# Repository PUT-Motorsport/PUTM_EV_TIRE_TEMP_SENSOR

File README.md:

# Tire Temperature Sensor v3.0

**TTS** (Tire Temperature Sensor) is a PCB designed to measure the temperature quickly, at a distance, and without the need to touch the wheels. The 4x16 pixel IR camera is used to obtain the data. It communicates with the STM microprocessor via the I2C protocol. Data is then averaged out to a 1x8 array of unsigned ints and sent with the CAN Transceiver to the car’s CAN network. This array can be then read off of the telemetry system implemented in the PM-08 racing car.

## Applications

While driving, a tire heats up. Heat dissipates differently across its surface and its rate changes depending on many factors (E.g. weather conditions or reoccurring acceleration). As a tire has its maximal temperature, exceeding this value may weaken its structural strength and cause its destruction in the worst-case scenario. This IR Camera PCB makes it possible to monitor a tire across its whole surface and prevent any damage associated with the temperature. As TTS monitors every wheel out of 4, our crew can easily detect if tires wear unevenly or excessively. Tire temperature patterns inform whether the car is properly calibrated, as the out-of-tune suspension causes tires to heat up significantly faster. This may result in grip loss in these areas.

## Core features

* 4x16 pixel MLX90621 thermal camera
* STM32G0C1KCT
* 24V to 3.3V buck converter
* 3.3V to 2.6V LDO
* 3.3V Isolated CAN transceiver
* Overcurrent and reverse polarity protection
* Status LEDs

## PCB

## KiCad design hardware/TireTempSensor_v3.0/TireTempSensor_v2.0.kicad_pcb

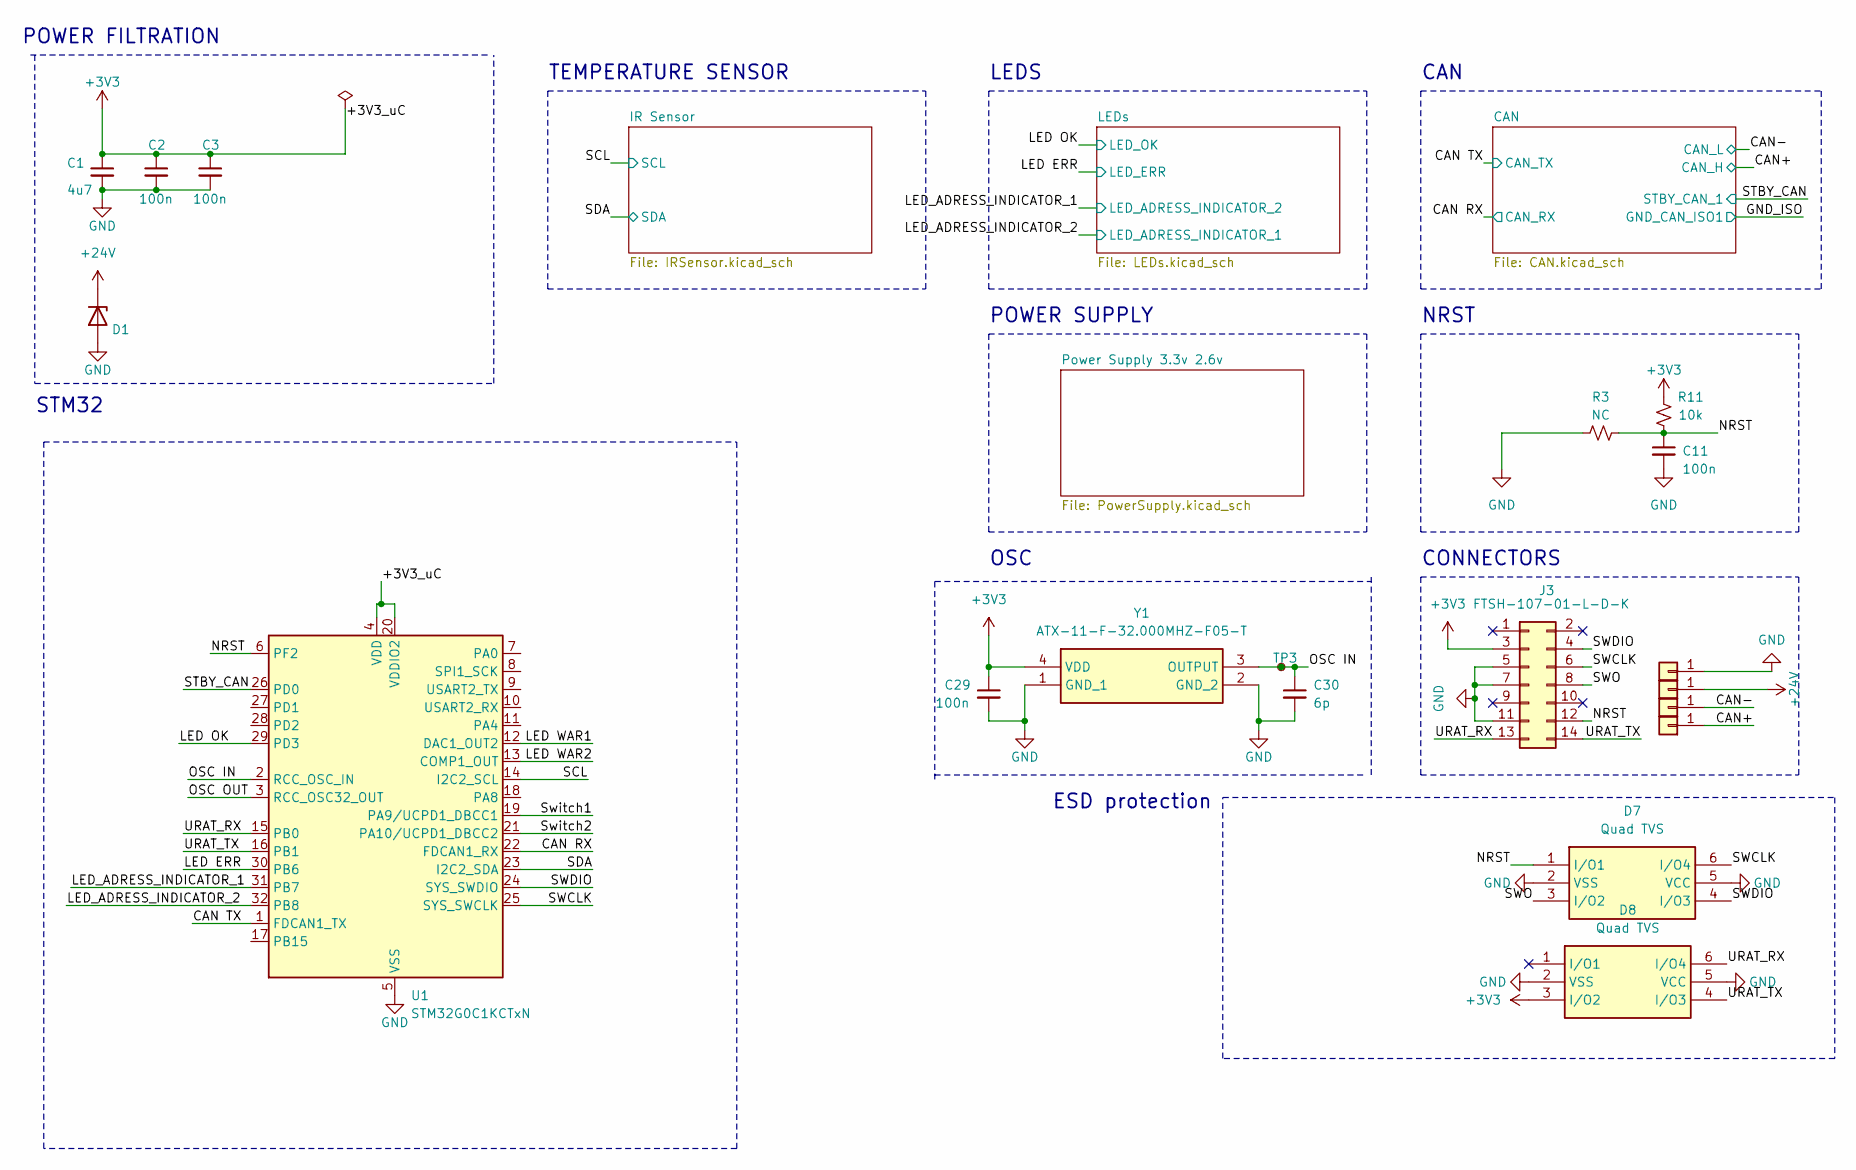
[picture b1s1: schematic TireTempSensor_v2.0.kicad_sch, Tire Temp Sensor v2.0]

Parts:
C1: 4u7; C_0603_1608Metric_Pad1.08x0.95mm_HandSolder; Mouser Part Number 81-ZRB18AR6YA475KE5L
C2, C3, C11, C29: 100n; C_0603_1608Metric_Pad1.08x0.95mm_HandSolder; Mouser Part Number 81-GCJ188R71H104MA2D
C30: 6p; C_0603_1608Metric_Pad1.08x0.95mm_HandSolder
D1: 30V; D_SOD-123
D7, D8: Quad TVS; SOT95P285X140-6N; Mouser Part Number 621-D5V0P4UR6SO-7
J1, J2, J4, J5: Conn_01x01; SolderWire-0.1sqmm_1x01_D0.4mm_OD1mm_Relief
J3: FTSH-107-01-L-D-K; FTSH-107-XX-YYY-DV-K; Mouser Part Number 200-FTSH10701LDK
R3: NC; R_0402_1005Metric
R11: 10k; R_0603_1608Metric
TP3: TestPoint_Small; TestPoint_Pad_D1.0mm
U1: STM32G0C1KCTxN; LQFP-32_7x7mm_P0.8mm
Y1: ATX-11-F-32.000MHZ-F05-T; ATX11F32000MHZF05T; Mouser Part Number 815-ATX11F32000MF05T

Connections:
+3V3: C1.1, C2.1, C3.1, C29.1, D8.3 (I/O2), J3.3, R11.2, U1.4 (VDD), U1.20 (VDDIO2), Y1.4 (VDD); also elsewhere on the board
+24V: D1.1 (K), J2.1; also elsewhere on the board
/CAN RX: U1.22 (FDCAN1_RX); also elsewhere on the board
/CAN TX: U1.1 (FDCAN1_TX); also elsewhere on the board
/CAN+: J5.1; also elsewhere on the board
/CAN-: J4.1; also elsewhere on the board
/LED ERR: U1.30 (PB6); also elsewhere on the board
/LED OK: U1.29 (PD3); also elsewhere on the board
/LED WAR1: U1.12 (DAC1_OUT2)
/LED WAR2: U1.13 (COMP1_OUT)
/LED_ADRESS_INDICATOR_1: U1.31 (PB7); also elsewhere on the board
/LED_ADRESS_INDICATOR_2: U1.32 (PB8); also elsewhere on the board
/NRST: C11.1, D7.1 (I/O1), J3.12, R3.2, R11.1, U1.6 (PF2)
/OSC IN: C30.1, TP3.1, U1.2 (RCC_OSC_IN), Y1.3 (OUTPUT)
/OSC OUT: U1.3 (RCC_OSC32_OUT)
/SCL: U1.14 (I2C2_SCL); also elsewhere on the board
/SDA: U1.23 (I2C2_SDA); also elsewhere on the board
/STBY_CAN: U1.26 (PD0); also elsewhere on the board
/SWCLK: D7.6 (I/O4), J3.6, U1.25 (SYS_SWCLK)
/SWDIO: D7.4 (I/O3), J3.4, U1.24 (SYS_SWDIO)
/SWO: D7.3 (I/O2), J3.8
/Switch1: U1.19 (PA9/UCPD1_DBCC1)
/Switch2: U1.21 (PA10/UCPD1_DBCC2)
/URAT_RX: D8.6 (I/O4), J3.13, U1.15 (PB0)
/URAT_TX: D8.4 (I/O3), J3.14, U1.16 (PB1)
GND: C1.2, C2.2, C3.2, C11.2, C29.2, C30.2, D1.2 (A), D7.2 (VSS), D7.5 (VCC), D8.2 (VSS), D8.5 (VCC), J1.1, J3.5, J3.7, J3.11, R3.1, U1.5 (VSS), Y1.1 (GND_1), Y1.2 (GND_2); also elsewhere on the board

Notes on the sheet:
NRST
POWER SUPPLY
ESD protection
OSC
STM32
CAN
POWER FILTRATION
LEDS
CONNECTORS
TEMPERATURE SENSOR

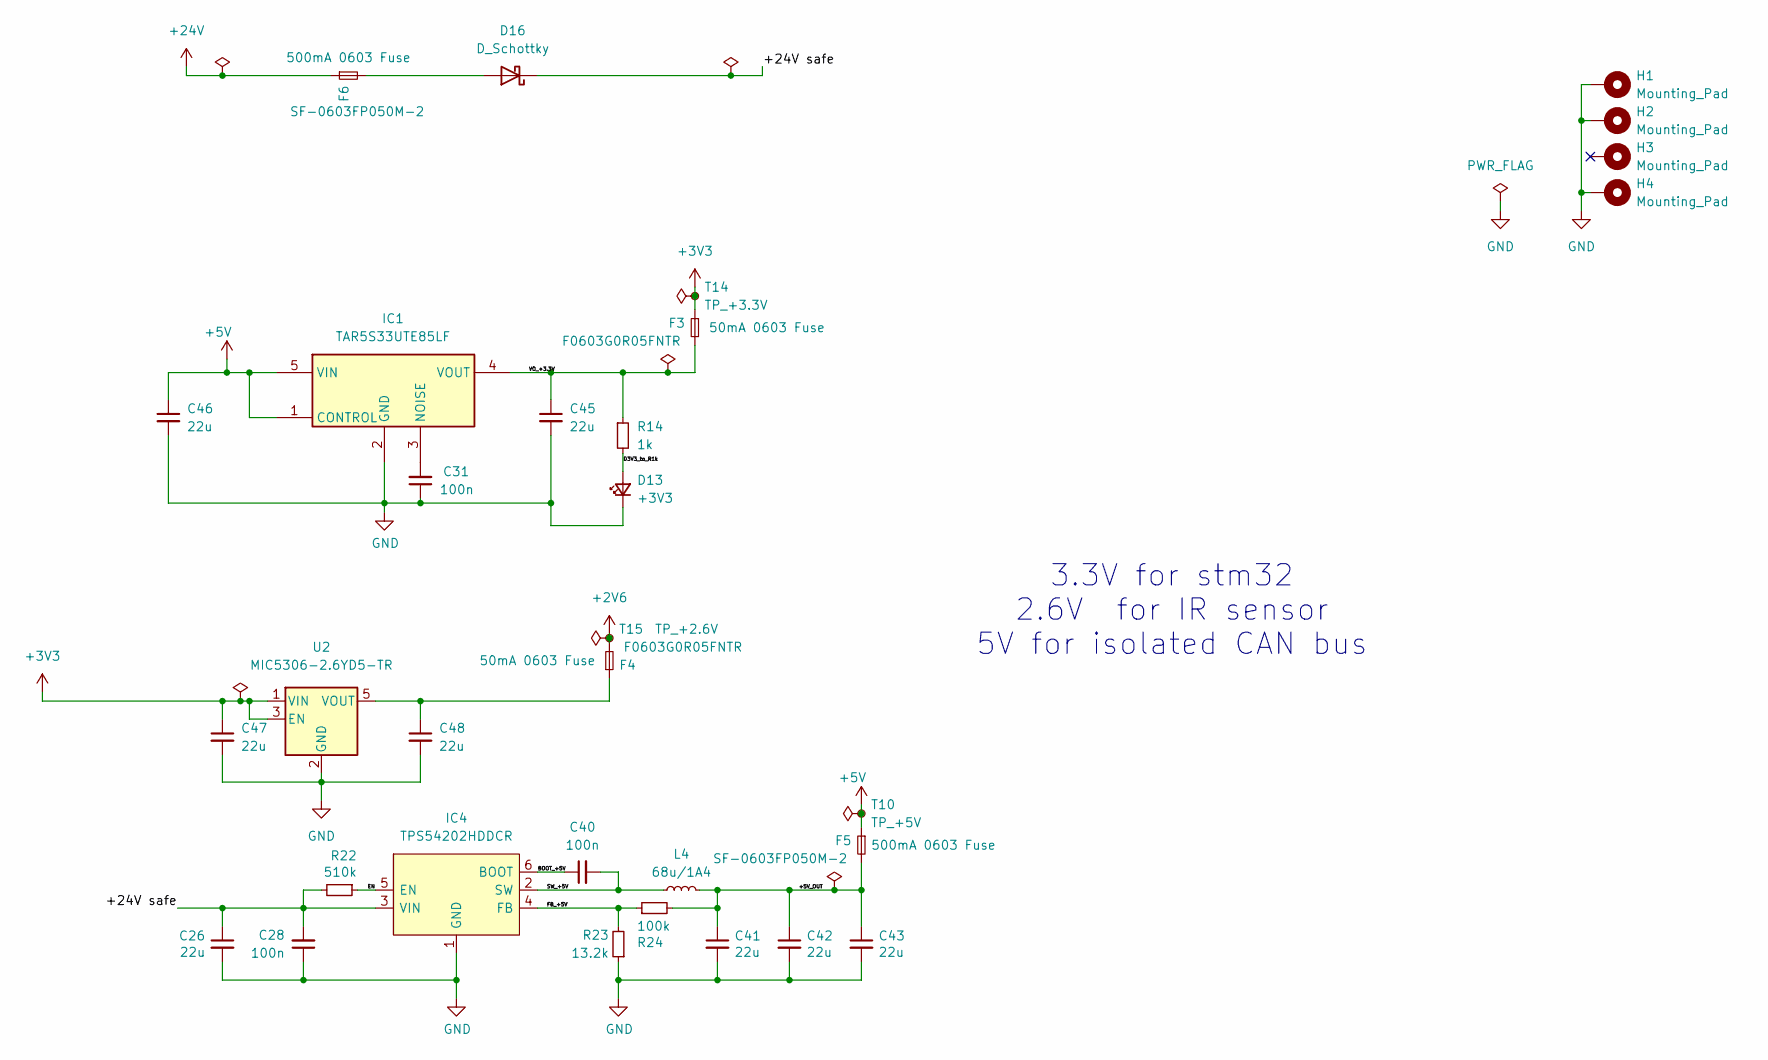
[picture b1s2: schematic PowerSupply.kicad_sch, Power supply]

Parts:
C26, C41, C42, C43: 22u; C_0805_2012Metric_Pad1.18x1.45mm_HandSolder; Manufacturer_Part_Number CL21A107MQYNNWE; Mouser Part Number 81-ZRA21CR61E226ME1L
C28, C31: 100n; C_0603_1608Metric_Pad1.08x0.95mm_HandSolder; Manufacturer_Part_Number C0603C104J3RACTU; Mouser Part Number 81-GCJ188R71H104MA2D
C40: 100n; C_0603_1608Metric_Pad1.08x0.95mm_HandSolder; Mouser Part Number 81-GCJ188R71H104MA2D
C45, C46, C47, C48: 22u; C_0805_2012Metric_Pad1.18x1.45mm_HandSolder; Mouser Part Number 81-ZRA21CR61E226ME1L
D13: +3V3; LED_0603_1608Metric_Pad1.05x0.95mm_HandSolder
D16: D_Schottky; D_0603_1608Metric_Pad1.05x0.95mm_HandSolder
F3, F4: F0603G0R05FNTR; Fuse_0603_1608Metric_Pad1.05x0.95mm_HandSolder
F5, F6: SF-0603FP050M-2; Fuse_0603_1608Metric_Pad1.05x0.95mm_HandSolder
H1, H2, H3, H4: Mounting_Pad; MountingHole_2.7mm_M2.5_ISO14580_Pad
IC1: TAR5S33UTE85LF; SOTFL65P210X75-5N; Mouser Part Number 757-TAR5S33UTE85LF
IC4: TPS54202HDDCR; SOT-23-6_Handsoldering; Mouser Part Number 595-TPS54202HDDCR
L4: 68u/1A4; L_Vishay_IFSC-1515AH_4x4x1.8mm; Mouser Part Number 810-VLS6045EX-680M
R14: 1k; R_0603_1608Metric_Pad0.98x0.95mm_HandSolder
R22: 510k; R_0603_1608Metric_Pad0.98x0.95mm_HandSolder; Manufacturer_Part_Number RT0603DRD07510KL; Mouser Part Number 603-RT0603DRD07510KL
R23: 13.2k; R_0603_1608Metric_Pad0.98x0.95mm_HandSolder; Manufacturer_Part_Number RT0603DRE0713K3L; Mouser Part Number 603-RT0603DRE0713K3L
R24: 100k; R_0603_1608Metric_Pad0.98x0.95mm_HandSolder; Manufacturer_Part_Number RT0603DRE07100KL; Mouser Part Number 603-RT0603DRE07100KL
T10: TP_+5V; TestPoint_Pad_1.0x1.0mm
T14: TP_+3.3V; TestPoint_Pad_1.0x1.0mm
T15: TP_+2.6V; TestPoint_Pad_1.0x1.0mm
U2: MIC5306-2.6YD5-TR; SOT-23-5

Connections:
+2V6: F4.2, T15.1; also elsewhere on the board
+3V3: C47.1, F3.1, T14.1, U2.1 (VIN), U2.3 (EN); also elsewhere on the board
+5V: C46.1, F5.1, IC1.1 (CONTROL), IC1.5 (VIN), T10.1; also elsewhere on the board
+24V: F6.1; also elsewhere on the board
/Power Supply 3.3v 2.6v/+5V_OUT: C41.1, C42.1, C43.1, F5.2, L4.2, R24.2
/Power Supply 3.3v 2.6v/+24V safe: C26.1, C28.2, D16.1 (K), IC4.3 (VIN), R22.2
/Power Supply 3.3v 2.6v/BOOT_+5V: C40.1, IC4.6 (BOOT)
/Power Supply 3.3v 2.6v/D3V3_to_R1k: D13.2 (A), R14.2
/Power Supply 3.3v 2.6v/EN: IC4.5 (EN), R22.1
/Power Supply 3.3v 2.6v/FB_+5V: IC4.4 (FB), R23.2, R24.1
/Power Supply 3.3v 2.6v/SW_+5V: C40.2, IC4.2 (SW), L4.1
/Power Supply 3.3v 2.6v/VO_+3.3V: C45.1, F3.2, IC1.4 (VOUT), R14.1
GND: C26.2, C28.1, C31.1, C41.2, C42.2, C43.2, C45.2, C46.2, C47.2, C48.2, D13.1 (K), H1.1, H2.1, H4.1, IC1.2 (GND), IC4.1 (GND), R23.1, U2.2 (GND); also elsewhere on the board
unnamed: D16.2 (A), F6.2
unnamed: C31.2, IC1.3 (NOISE)
unnamed: C48.1, F4.1, U2.5 (VOUT)

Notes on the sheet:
3.3V for stm32 2.6V for IR sensor 5V for isolated CAN bus

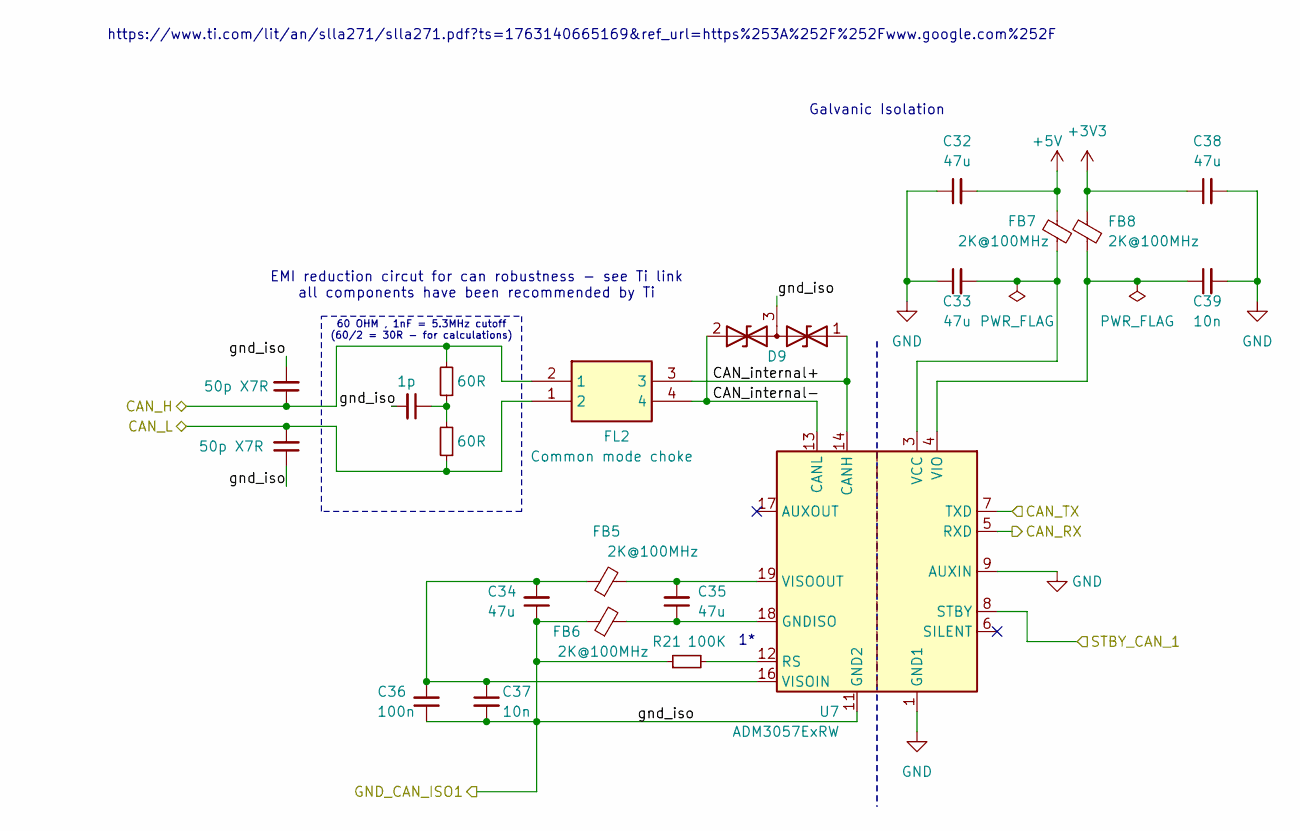
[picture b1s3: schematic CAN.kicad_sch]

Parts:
C32, C33, C34, C35, C38: 47u; C_0805_2012Metric_Pad1.18x1.45mm_HandSolder
C36: 100n; C_0603_1608Metric_Pad1.08x0.95mm_HandSolder; Mouser Part Number 81-GCJ188R71H104MA2D
C37, C39: 10n; C_0603_1608Metric_Pad1.08x0.95mm_HandSolder
C44: 1p; C_0805_2012Metric_Pad1.18x1.45mm_HandSolder
C50, C51: 50p X7R; C_0805_2012Metric_Pad1.18x1.45mm_HandSolder
D9: D_TVS_Dual_AAC; SOT-23_Handsoldering
FB5, FB6, FB7, FB8: 2K@100MHz; L_0805_2012Metric_Pad1.05x1.20mm_HandSolder
FL2: Common mode choke; DR331513BE; Mouser Part Number 652-DR331-513AE
R21: 100K; R_0603_1608Metric_Pad0.98x0.95mm_HandSolder
R25, R26: 60R; R_0603_1608Metric_Pad0.98x0.95mm_HandSolder
U7: ADM3057ExRW; SOIC-20W_7.5x12.8mm_P1.27mm

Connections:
+3V3: C38.1, FB8.2; also elsewhere on the board
+5V: C32.2, FB7.2; also elsewhere on the board
/CAN RX: U7.5 (RXD); also elsewhere on the board
/CAN TX: U7.7 (TXD); also elsewhere on the board
/CAN+: C51.1, FL2.2 (1), R25.2; also elsewhere on the board
/CAN-: C50.2, FL2.1 (2), R26.1; also elsewhere on the board
/CAN/CAN_internal+: D9.1 (A1), FL2.3, U7.14 (CANH)
/CAN/CAN_internal-: D9.2 (A2), FL2.4, U7.13 (CANL)
/GND_ISO: C34.1, C36.1, C37.2, C44.2, C50.1, C51.2, D9.3 (common), FB6.1, R21.1, U7.11 (GND2), U7.15 (GND2)
/STBY_CAN: U7.8 (STBY); also elsewhere on the board
GND: C32.1, C33.1, C38.2, C39.2, U7.1 (GND1), U7.2 (GND1), U7.9 (AUXIN), U7.10 (GND1); also elsewhere on the board
unnamed: C35.1, FB6.2, U7.18 (GNDISO), U7.20 (GNDISO)
unnamed: C44.1, R25.1, R26.2
unnamed: R21.2, U7.12 (RS)
unnamed: C33.2, FB7.1, U7.3 (VCC)
unnamed: C39.1, FB8.1, U7.4 (VIO)
unnamed: C34.2, C36.2, C37.1, FB5.1, U7.16 (VISOIN)
unnamed: C35.2, FB5.2, U7.19 (VISOOUT)

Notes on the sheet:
EMI reduction circut for can robustness - see Ti link all components have been recommended by Ti
https://www.ti.com/lit/an/slla271/slla271.pdf?ts=1763140665169&ref_url=https%253A%252F%252Fwww.google.com%252F
Galvanic Isolation
60 OHM , 1nF = 5.3MHz cutoff (60/2 = 30R - for calculations)

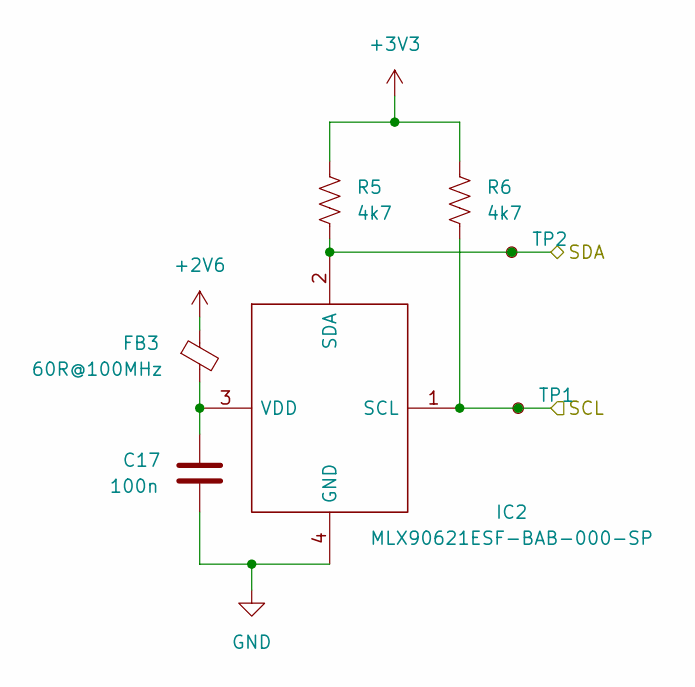
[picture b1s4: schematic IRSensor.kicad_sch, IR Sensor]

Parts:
C17: 100n; C_0603_1608Metric_Pad1.08x0.95mm_HandSolder; Mouser Part Number 81-GCJ188R71H104MA2D
FB3: 60R@100MHz; L_0603_1608Metric
IC2: MLX90621ESF-BAB-000-SP; MLX90621ESFBAB000SP; Manufacturer_Part_Number MLX90621ESF-BAB-000-SP; Mouser Part Number 482-90621ESFBAB000SP
R5, R6: 4k7; R_0603_1608Metric
TP1, TP2: TestPoint_Small; TestPoint_Pad_D1.0mm

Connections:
+2V6: FB3.1; also elsewhere on the board
+3V3: R5.1, R6.1; also elsewhere on the board
/SCL: IC2.1 (SCL), R6.2, TP1.1; also elsewhere on the board
/SDA: IC2.2 (SDA), R5.2, TP2.1; also elsewhere on the board
GND: C17.2, IC2.4 (GND); also elsewhere on the board
unnamed: C17.1, FB3.2, IC2.3 (VDD)

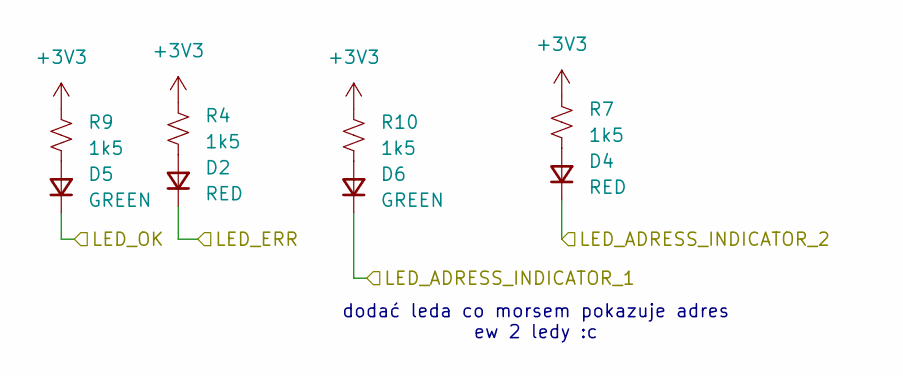
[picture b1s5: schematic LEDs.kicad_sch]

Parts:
D2, D4: RED; D_0603_1608Metric
D5, D6: GREEN; D_0603_1608Metric
R4, R7, R9, R10: 1k5; R_0603_1608Metric

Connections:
+3V3: R4.1, R7.1, R9.1, R10.1; also elsewhere on the board
/LED ERR: D2.1 (K); also elsewhere on the board
/LED OK: D5.1 (K); also elsewhere on the board
/LED_ADRESS_INDICATOR_1: D4.1 (K); also elsewhere on the board
/LED_ADRESS_INDICATOR_2: D6.1 (K); also elsewhere on the board
unnamed: D2.2 (A), R4.2
unnamed: D4.2 (A), R7.2
unnamed: D5.2 (A), R9.2
unnamed: D6.2 (A), R10.2

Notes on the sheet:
dodać leda co morsem pokazuje adres ew 2 ledy :c

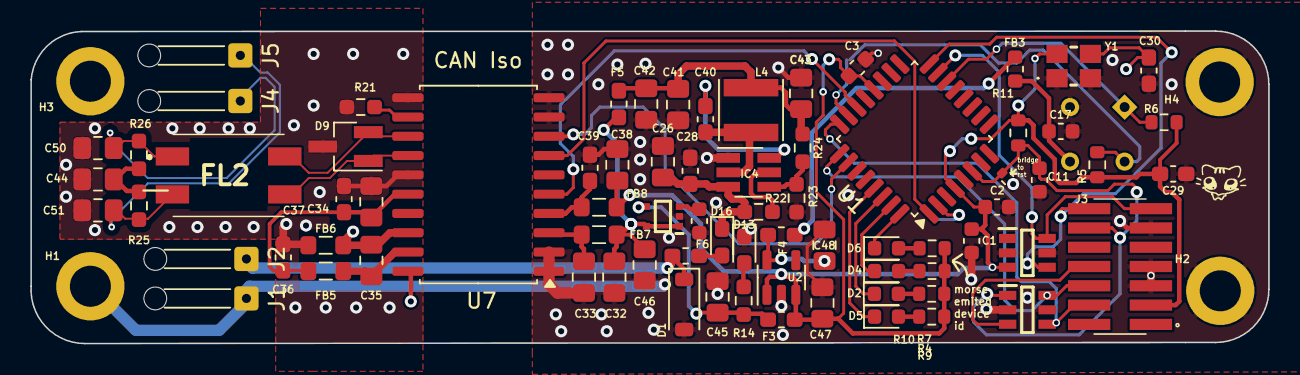
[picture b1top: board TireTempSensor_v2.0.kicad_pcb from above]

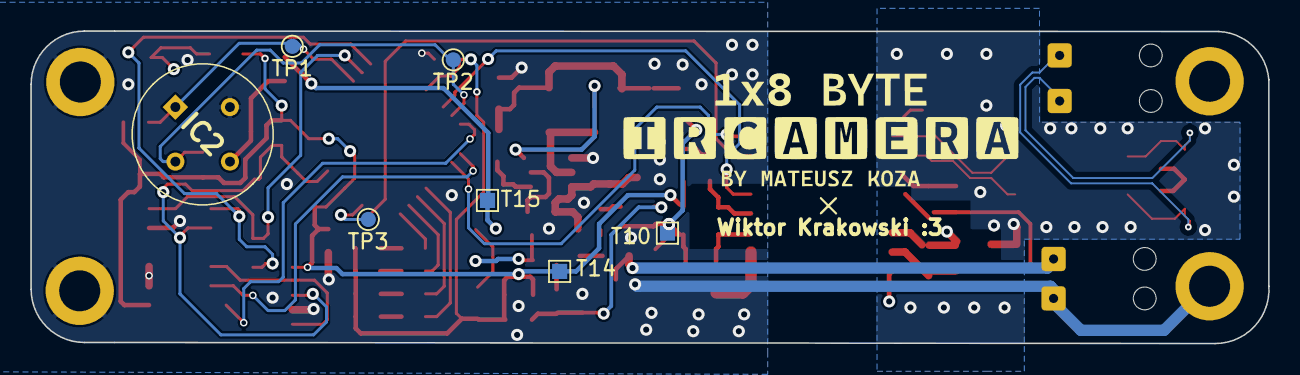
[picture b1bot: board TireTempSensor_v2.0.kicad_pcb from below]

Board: 4 copper layers, 81.5 x 20.6 mm, 87 parts (7 on the bottom side), 49 nets.

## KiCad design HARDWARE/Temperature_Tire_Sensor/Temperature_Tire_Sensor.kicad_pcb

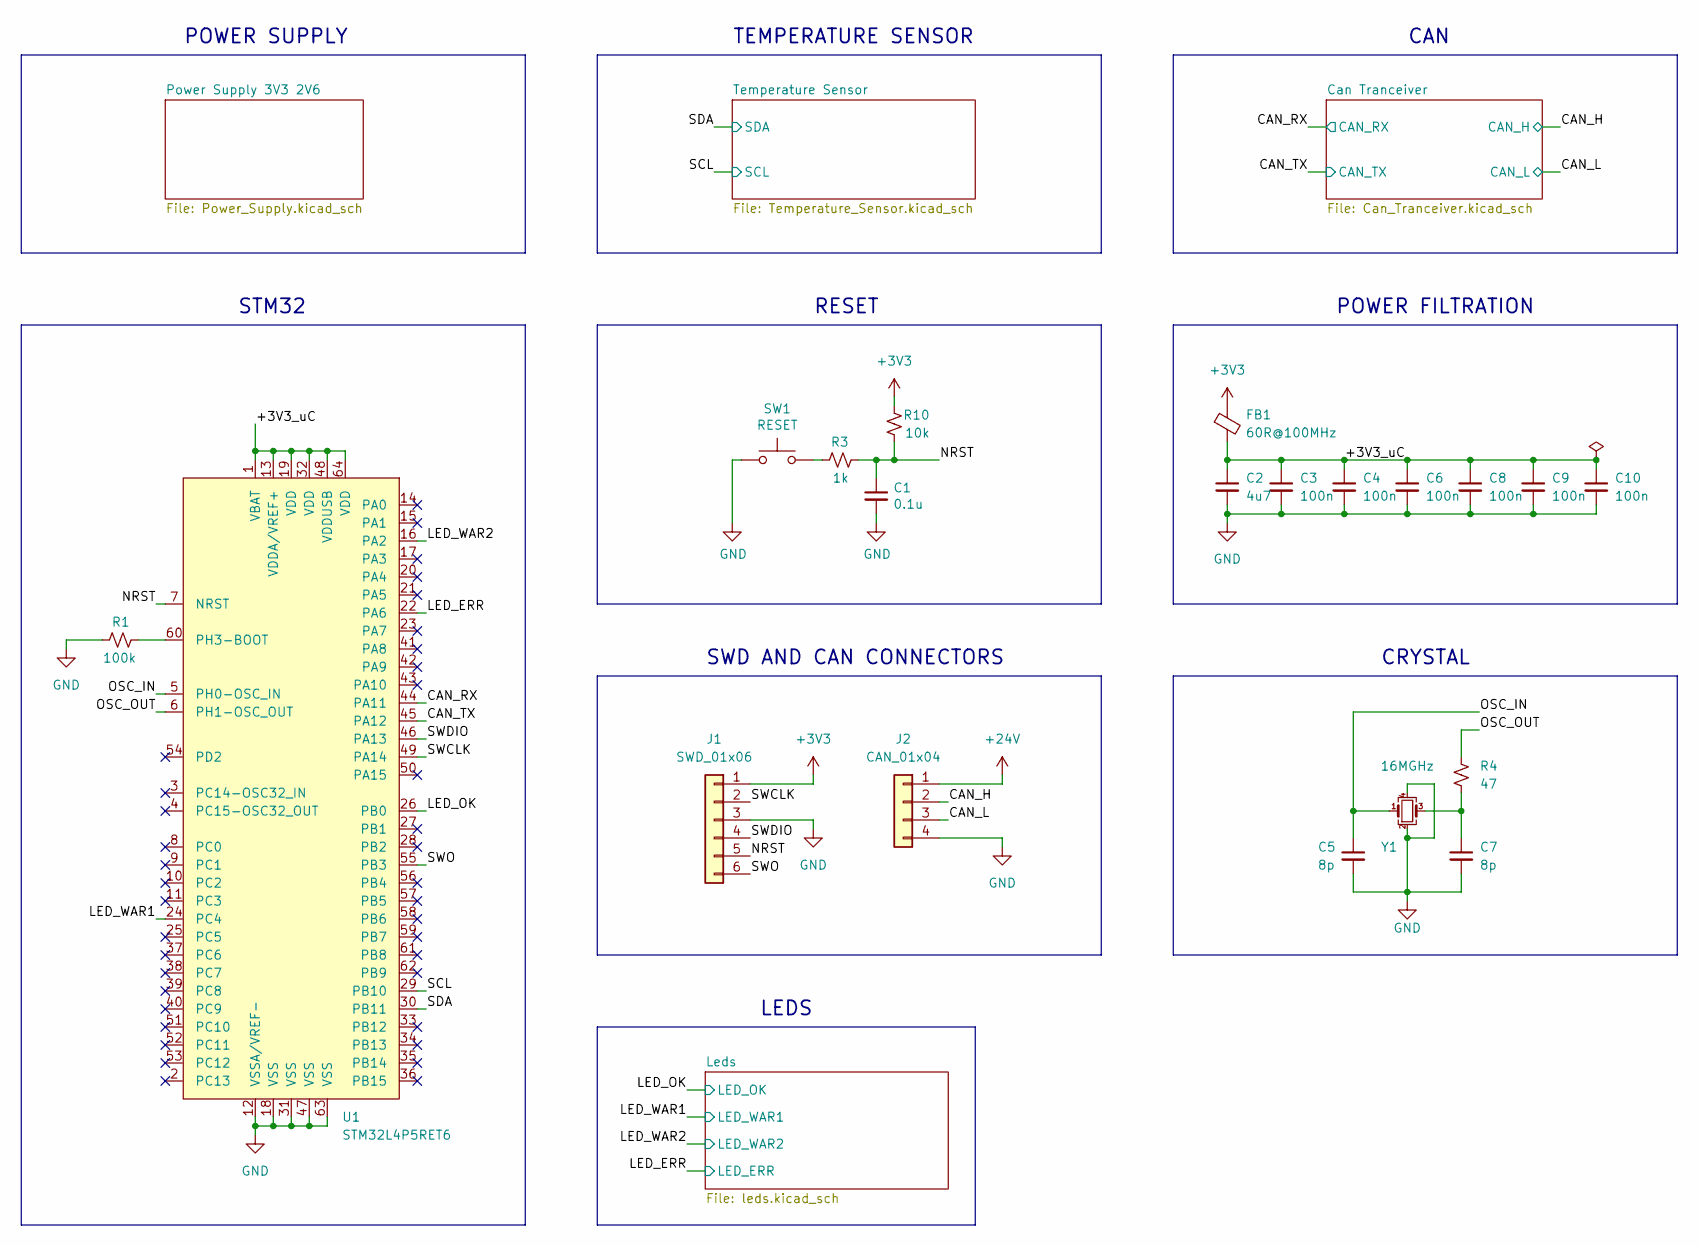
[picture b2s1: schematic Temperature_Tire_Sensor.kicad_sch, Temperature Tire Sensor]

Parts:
C1: 0.1u; C_0603_1608Metric
C2: 4u7; C_0603_1608Metric
C3, C4, C6, C8, C9, C10: 100n; C_0603_1608Metric
C5, C7: 8p; C_0603_1608Metric
FB1: 60R@100MHz; L_0603_1608Metric
J1: SWD_01x06; PinHeader_1x06_P2.54mm_Vertical
J2: CAN_01x04; SolderWirePad_1x04_SMD_1x2mm
R1: 100k; R_0603_1608Metric
R3: 1k; R_0603_1608Metric
R4: 47; R_0603_1608Metric
R10: 10k; R_0603_1608Metric
SW1: RESET; 434781025816
U1: STM32L4P5RET6; LQFP-64_10x10mm_P0.5mm
Y1: 16MGHz; Crystal_SMD_SeikoEpson_TSX3225-4Pin_3.2x2.5mm

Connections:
+3V3: FB1.1, J1.1, R10.2; also elsewhere on the board
+24V: J2.1; also elsewhere on the board
/+3V3_uC: C2.1, C3.1, C4.1, C6.1, C8.1, C9.1, C10.1, FB1.2, U1.1 (VBAT), U1.13 (VDDA/VREF+), U1.19 (VDD), U1.32 (VDD), U1.48 (VDDUSB), U1.64 (VDD)
/CAN_H: J2.2; also elsewhere on the board
/CAN_L: J2.3; also elsewhere on the board
/CAN_RX: U1.44 (PA11); also elsewhere on the board
/CAN_TX: U1.45 (PA12); also elsewhere on the board
/LED_ERR: U1.22 (PA6); also elsewhere on the board
/LED_OK: U1.26 (PB0); also elsewhere on the board
/LED_WAR1: U1.24 (PC4); also elsewhere on the board
/LED_WAR2: U1.16 (PA2); also elsewhere on the board
/NRST: C1.1, J1.5, R3.2, R10.1, U1.7 (NRST)
/OSC_IN: C5.1, U1.5 (PH0-OSC_IN), Y1.1
/OSC_OUT: R4.1, U1.6 (PH1-OSC_OUT)
/SCL: U1.29 (PB10); also elsewhere on the board
/SDA: U1.30 (PB11); also elsewhere on the board
/SWCLK: J1.2, U1.49 (PA14)
/SWDIO: J1.4, U1.46 (PA13)
/SWO: J1.6, U1.55 (PB3)
GND: C1.2, C2.2, C3.2, C4.2, C5.2, C6.2, C7.2, C8.2, C9.2, C10.2, J1.3, J2.4, R1.2, SW1.1, U1.12 (VSSA/VREF-), U1.18 (VSS), U1.31 (VSS), U1.47 (VSS), U1.63 (VSS), Y1.2, Y1.4; also elsewhere on the board
unnamed: C7.1, R4.2, Y1.3
unnamed: R1.1, U1.60 (PH3-BOOT)
unnamed: R3.1, SW1.2

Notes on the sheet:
CAN
CRYSTAL
SWD AND CAN CONNECTORS
TEMPERATURE SENSOR
LEDS
RESET
STM32
POWER FILTRATION
POWER SUPPLY

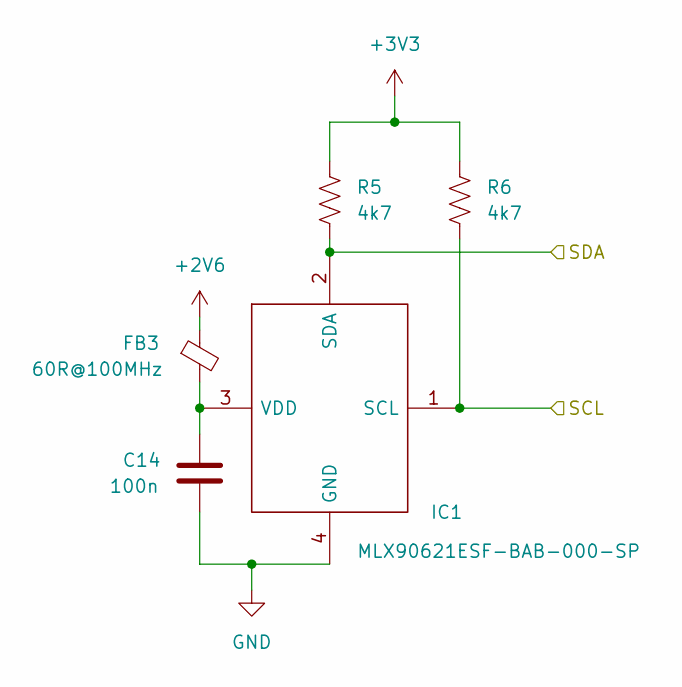
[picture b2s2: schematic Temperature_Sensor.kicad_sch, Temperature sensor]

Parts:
C14: 100n; C_0603_1608Metric
FB3: 60R@100MHz; L_0603_1608Metric
IC1: MLX90621ESF-BAB-000-SP; MLX90621ESFBAB000SP; Manufacturer_Part_Number MLX90621ESF-BAB-000-SP; Mouser Part Number 482-90621ESFBAB000SP
R5, R6: 4k7; R_0603_1608Metric

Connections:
+2V6: FB3.1; also elsewhere on the board
+3V3: R5.1, R6.1; also elsewhere on the board
/SCL: IC1.1 (SCL), R6.2; also elsewhere on the board
/SDA: IC1.2 (SDA), R5.2; also elsewhere on the board
GND: C14.2, IC1.4 (GND); also elsewhere on the board
unnamed: C14.1, FB3.2, IC1.3 (VDD)

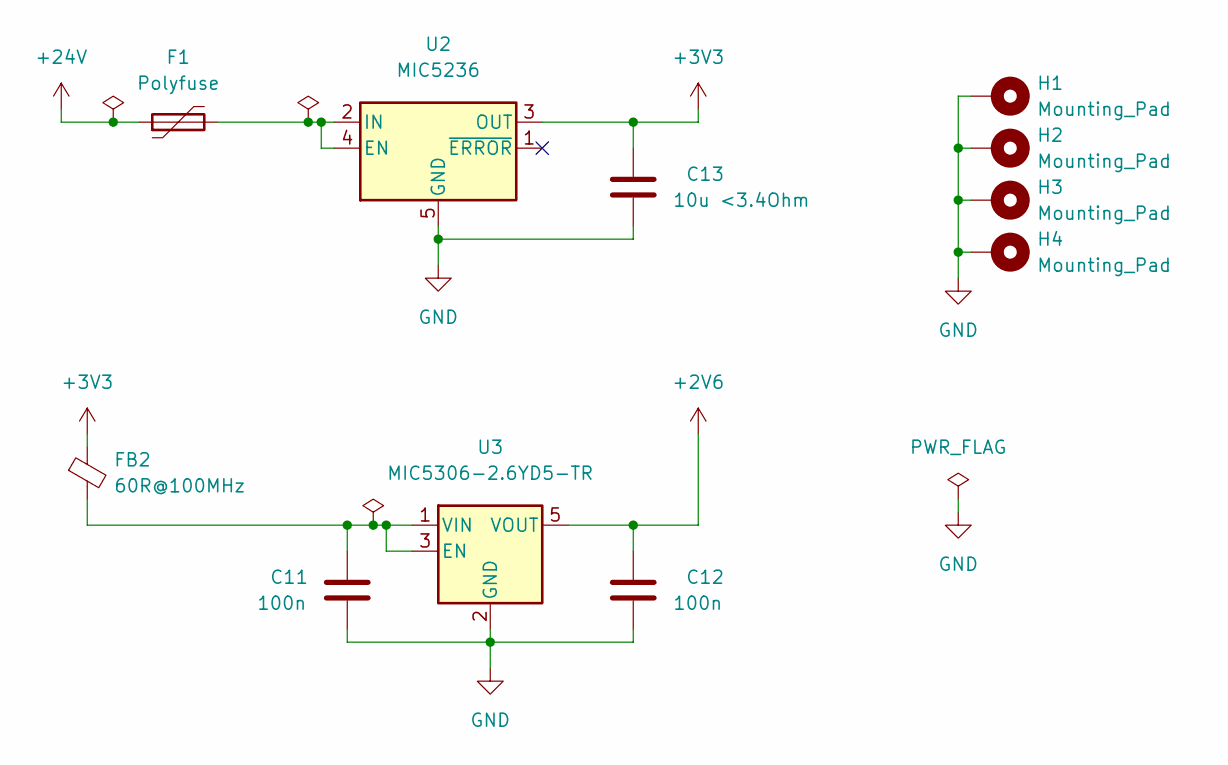
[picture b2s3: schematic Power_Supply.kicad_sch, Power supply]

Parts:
C11, C12: 100n; C_0603_1608Metric
C13: 10u <3.4Ohm; C_0603_1608Metric
F1: Polyfuse; Fuse_0805_2012Metric
FB2: 60R@100MHz; L_0603_1608Metric
H1, H2, H3, H4: Mounting_Pad; MountingHole_2.7mm_M2.5_ISO14580_Pad
U2: MIC5236; SOIC-8_3.9x4.9mm_P1.27mm
U3: MIC5306-2.6YD5-TR; TSOT-23-5

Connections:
+2V6: C12.1, U3.5 (VOUT); also elsewhere on the board
+3V3: C13.1, FB2.1, U2.3 (OUT); also elsewhere on the board
+24V: F1.1; also elsewhere on the board
GND: C11.2, C12.2, C13.2, H1.1, H2.1, H3.1, H4.1, U2.5 (GND), U2.6 (GND), U2.7 (GND), U2.8 (GND), U3.2 (GND); also elsewhere on the board
unnamed: C11.1, FB2.2, U3.1 (VIN), U3.3 (EN)
unnamed: F1.2, U2.2 (IN), U2.4 (EN)

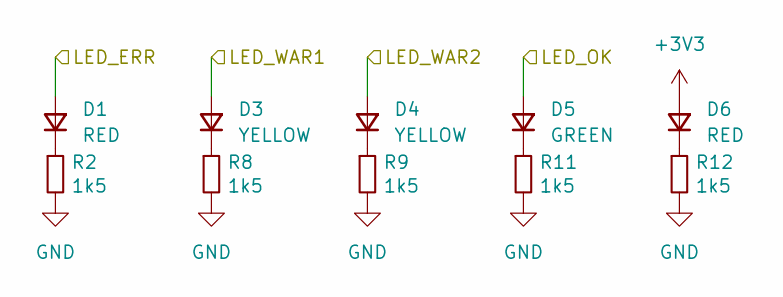
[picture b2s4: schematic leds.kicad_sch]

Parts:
D1, D6: RED; D_0603_1608Metric
D3, D4: YELLOW; D_0603_1608Metric
D5: GREEN; D_0603_1608Metric
R2, R8, R9, R11, R12: 1k5; R_0603_1608Metric

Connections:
+3V3: D6.2 (A); also elsewhere on the board
/LED_ERR: D1.2 (A); also elsewhere on the board
/LED_OK: D5.2 (A); also elsewhere on the board
/LED_WAR1: D3.2 (A); also elsewhere on the board
/LED_WAR2: D4.2 (A); also elsewhere on the board
GND: R2.2, R8.2, R9.2, R11.2, R12.2; also elsewhere on the board
unnamed: D1.1 (K), R2.1
unnamed: D3.1 (K), R8.1
unnamed: D4.1 (K), R9.1
unnamed: D5.1 (K), R11.1
unnamed: D6.1 (K), R12.1

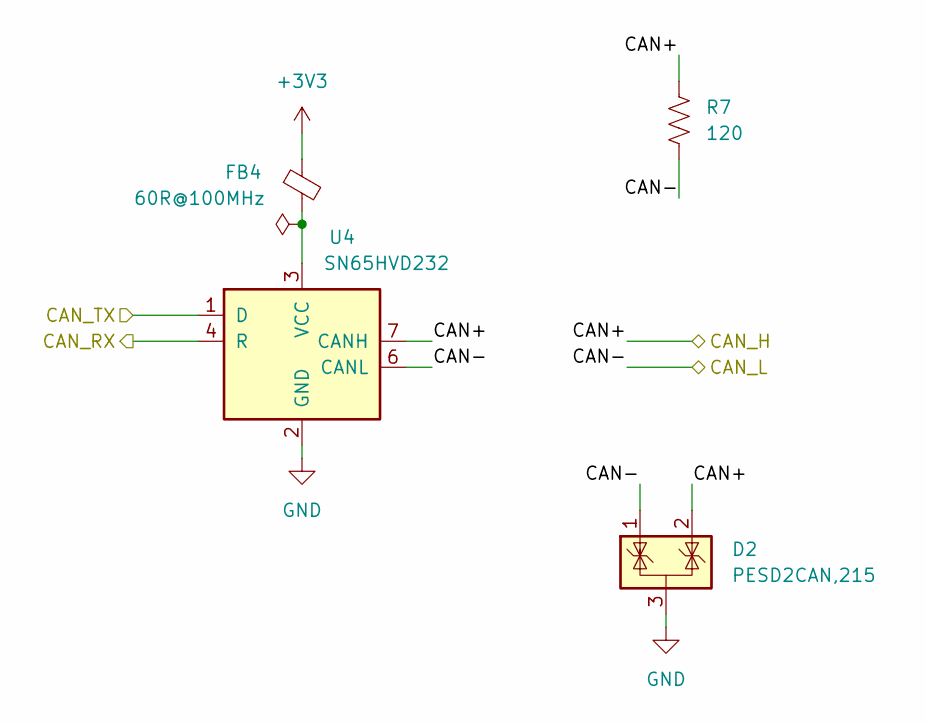
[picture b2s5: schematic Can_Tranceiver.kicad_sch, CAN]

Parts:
D2: PESD2CAN,215; SOT-23
FB4: 60R@100MHz; L_0603_1608Metric
R7: 120; R_0603_1608Metric
U4: SN65HVD232; SOIC-8_3.9x4.9mm_P1.27mm

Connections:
+3V3: FB4.1; also elsewhere on the board
/CAN_H: D2.2 (K), R7.1, U4.7 (CANH); also elsewhere on the board
/CAN_L: D2.1 (K), R7.2, U4.6 (CANL); also elsewhere on the board
/CAN_RX: U4.4 (R); also elsewhere on the board
/CAN_TX: U4.1 (D); also elsewhere on the board
GND: D2.3 (A), U4.2 (GND); also elsewhere on the board
unnamed: FB4.2, U4.3 (VCC)

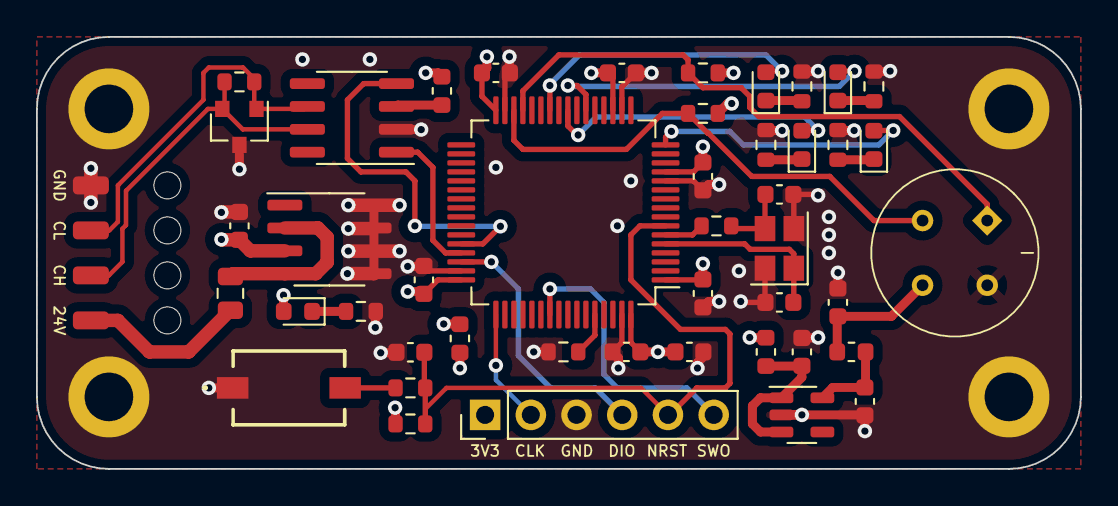
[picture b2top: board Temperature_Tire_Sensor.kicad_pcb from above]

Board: 4 copper layers, 58.0 x 24.0 mm, 50 parts (0 on the bottom side), 33 nets.

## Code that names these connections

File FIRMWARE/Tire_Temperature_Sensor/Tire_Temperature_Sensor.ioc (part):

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Mcu.Name=STM32L4P5R(G-E)Tx
Mcu.Package=LQFP64
Mcu.UserName=STM32L4P5RETx
PA11.Mode=CAN_Activate
PA11.Signal=CAN1_RX
PA12.Mode=CAN_Activate
PA12.Signal=CAN1_TX
PA13\ (JTMS/SWDIO).Mode=Trace_Asynchronous_SW
PA13\ (JTMS/SWDIO).Signal=SYS_JTMS-SWDIO
PA14\ (JTCK/SWCLK).Mode=Trace_Asynchronous_SW
PA14\ (JTCK/SWCLK).Signal=SYS_JTCK-SWCLK
PA2.GPIOParameters=GPIO_Label
PA2.GPIO_Label=LED_WAR2
PA2.Signal=GPIO_Output
PA6.GPIOParameters=GPIO_Label
PA6.GPIO_Label=LED_ERR
PA6.Signal=GPIO_Output
PB0.GPIOParameters=GPIO_Label
PB0.GPIO_Label=LED_OK
PB0.Signal=GPIO_Output
PB10.Mode=I2C
PB10.Signal=I2C2_SCL
PB11.Mode=I2C
PB11.Signal=I2C2_SDA
PB3\ (JTDO/TRACESWO).Mode=Trace_Asynchronous_SW
PB3\ (JTDO/TRACESWO).Signal=SYS_JTDO-SWO
PC4.GPIOParameters=GPIO_Label
PC4.GPIO_Label=LED_WAR1
PC4.Signal=GPIO_Output
PH0-OSC_IN\ (PH0).Mode=HSE-External-Oscillator
PH0-OSC_IN\ (PH0).Signal=RCC_OSC_IN
PH1-OSC_OUT\ (PH1).Mode=HSE-External-Oscillator
PH1-OSC_OUT\ (PH1).Signal=RCC_OSC_OUT
RCC.HSE_VALUE=8000000
board=custom

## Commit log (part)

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2022-05-17 pcb layout nearly completed
2022-05-18 pcb layout is done/has to be checked
2022-05-25 Routing is done - has to be checked
2022-05-26 TTS V1.0 - needs to be checked
2022-06-13 Preproduction review.
2022-06-14 Silkscreen layout has been changed
2022-06-14 renders
2022-08-24 can be ordered
2022-10-21 footprint has been changed + some minor silkscreen changes
2025-09-30 Zmiany w schemacie: izolowany can, przetwornica na 5v dla CANA, zabezpieczenia przepięciowe, selektor adressu can
2025-10-05 Piotruś prosił :3
2025-10-07 Poprawki, kontynuacja layoutu
2025-10-07 Propozycja layoutu na spotkanie
2025-10-16 Nowy layout, nowe tvsy
2025-10-18 Gotowe do sprawdzenia
2025-10-18 Do sprawdzenia :3
2025-10-18 Do sprawdzenia :33
2025-10-18 Poprawiono SPI NA I2C
2025-10-23 Poprawione :3
2025-10-28 lekkie poprawki
2025-10-28 Zmieniono routing w celu zmniejszenia przecięć masy
2025-11-02 Piotrkowe poprawy
2025-11-10 updated silkscreen
2025-11-11 Z wielkim bólem przesunięte złącze aby poprawić routing cana
2025-11-15 Added aditional emi prevention measures
2025-11-23 Zmieniono ldo na 3.3V, dodano linki do mousera, gotowe na relase
2026-02-12 Nowy branch
2026-05-22 Jebany can
2026-05-22 rm mistake folder
2026-05-22 update modules file
2026-05-22 update submodules file
2026-05-22 update modules file v3
2026-05-22 add can lib
2026-06-04 Pierdolony skurwiony cmake nie działa, michał ratuuuuuuj
2026-06-04 make work cmake
2026-06-20 Hmm moze zadziała
2026-06-20 Wyglada jakby działało
2026-06-21 Działa, potwierdzone ts masterem :3
